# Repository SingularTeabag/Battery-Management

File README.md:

# **Battery-Management**
A repository to organize my battery management PCBs

## Single Cell 5 Volt Regulator

### Chips used
* [BQ25185DLHR](https://www.ti.com/product/BQ25185) - Battery Charging 
* [TPS61023DRLT](https://www.ti.com/product/TPS61023) - Voltage Regulation
* [MAX17048G](https://www.analog.com/en/products/max17048.html) - Fuel Gauge
### About 
This PCB is my first "real" PCB that I've designed from scratch using the datasheets of the three respective chips.
That aside this PCB is intended for easy battery support for prototyping with microcontroller development boards that require a stable 5 volt input. The board breaks out STAT1, STAT2, CE, and TS from BQ25185DLHR to allow data and control to the used microcontroller, and an external thermistor for battery safety. The board additionally has two pins meant to be used for an external on/off switch, marked on the back silkscreen. Like the battery charging IC the fuel gauges' data signals are also broken out to intended for use with the microcontroller. The USB type C port does not have it's data plus and data minus pins broken out, these are used as a differential pair which requires both wires to be exactly the same length and require impedance matching which all goes out the window when using external wires.

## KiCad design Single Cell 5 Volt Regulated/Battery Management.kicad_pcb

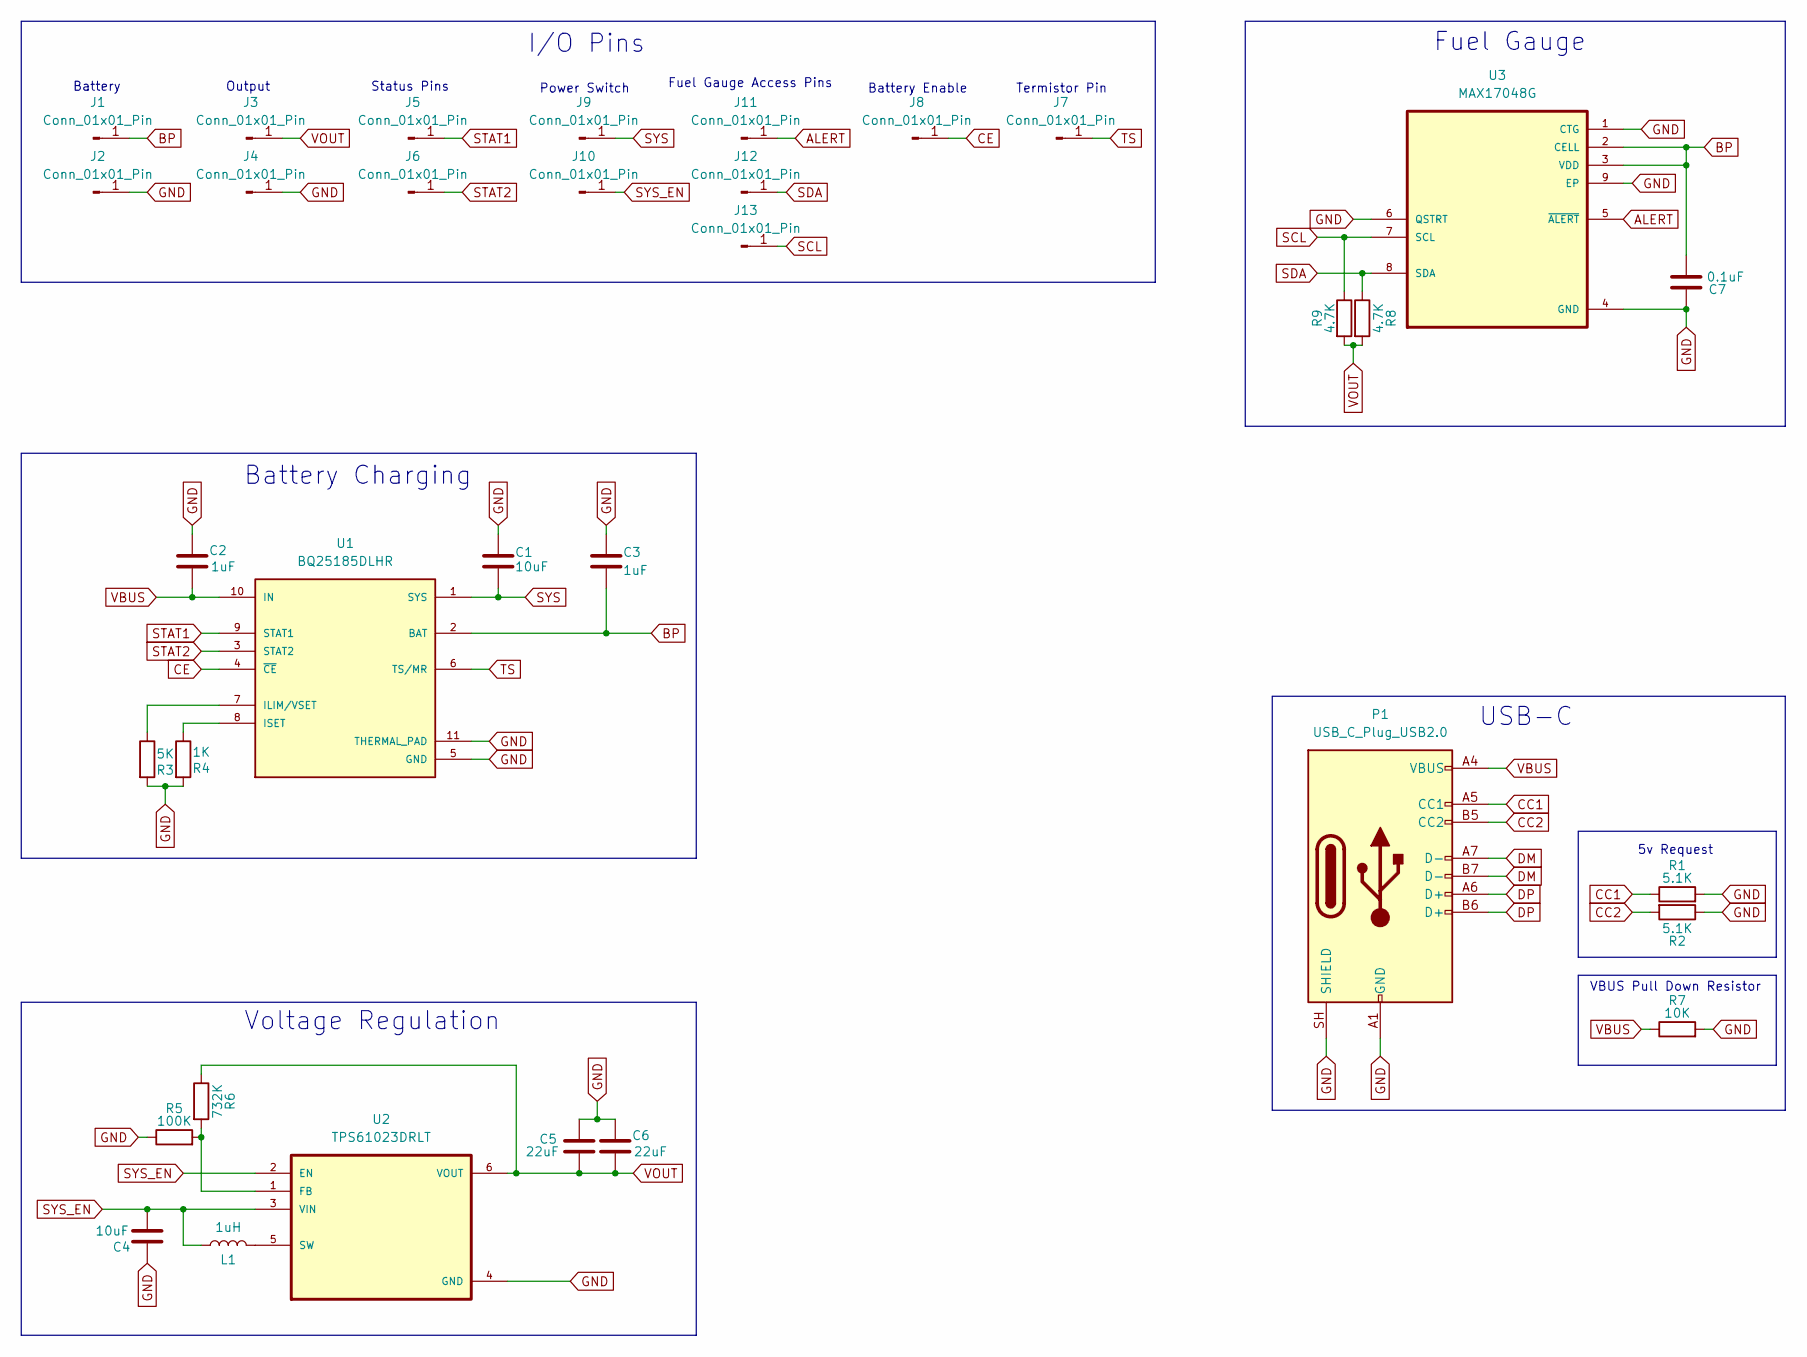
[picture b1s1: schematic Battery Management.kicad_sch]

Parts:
C1, C4: 10uF; C_0603_1608Metric
C2, C3: 1uF; C_0603_1608Metric
C5, C6: 22uF; C_0603_1608Metric
C7: 0.1uF; C_0603_1608Metric
J1, J3, J5, J6, J7, J8, J9, J10, J11, J12, J13: Conn_01x01_Pin; Connector Hole
J2, J4: Conn_01x01_Pin; Ground Hole
L1: 1uH; L_APV_ANR4030
P1: USB_C_Plug_USB2.0; USB_C_Receptacle_JAE_DX07S016JA1R1500
R1, R2: 5.1K; R_0603_1608Metric
R3: 5K; R_0603_1608Metric
R4: 1K; R_0603_1608Metric
R5: 100K; R_0603_1608Metric
R6: 732K; R_0603_1608Metric
R7: 10K; R_0603_1608Metric
R8, R9: 4.7K; R_0603_1608Metric
U1: BQ25185DLHR; IC_BQ25185DLHR; PARTREV OCTOBER 2023
U2: TPS61023DRLT; SOT50P160X60-6N
U3: MAX17048G; SON50P200X200X80-9N

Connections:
ALERT: J11.1 (Pin_1_1), U3.5 (~ALERT)
BP: C3.2, C7.1, J1.1 (Pin_1_1), U1.2 (BAT), U3.2 (CELL), U3.3 (VDD)
CC1: P1.A5 (CC1), R1.1
CC2: P1.B5 (CC2), R2.2
CE: J8.1 (Pin_1_1), U1.4 (~CE)
DM: P1.A7 (D-), P1.B7 (D-)
DP: P1.A6 (D+), P1.B6 (D+)
GND: C1.1, C2.1, C3.1, C4.1, C5.2, C6.1, C7.2, J2.1 (Pin_1_1), J4.1 (Pin_1_1), P1.A1 (GND), P1.A12 (GND), P1.B1 (GND), P1.B12 (GND), P1.SH (SHIELD), R1.2, R2.1, R3.2, R4.2, R5.1, R7.2, U1.5 (GND), U1.11 (THERMAL_PAD), U2.4 (GND), U3.1 (CTG), U3.4 (GND), U3.6 (QSTRT), U3.9 (EP)
unnamed: R3.1, U1.7 (ILIM/VSET)
unnamed: R4.1, U1.8 (ISET)
unnamed: R5.2, R6.2, U2.1 (FB)
unnamed: L1.2, U2.5 (SW)
SCL: J13.1 (Pin_1_1), R9.1, U3.7 (SCL)
SDA: J12.1 (Pin_1_1), R8.1, U3.8 (SDA)
STAT1: J5.1 (Pin_1_1), U1.9 (STAT1)
STAT2: J6.1 (Pin_1_1), U1.3 (STAT2)
SYS: C1.2, J9.1 (Pin_1_1), U1.1 (SYS)
SYS_EN: C4.2, J10.1 (Pin_1_1), L1.1, U2.2 (EN), U2.3 (VIN)
TS: J7.1 (Pin_1_1), U1.6 (TS/MR)
VBUS: C2.2, P1.A4 (VBUS), P1.A9 (VBUS), P1.B4 (VBUS), P1.B9 (VBUS), R7.1, U1.10 (IN)
VOUT: C5.1, C6.2, J3.1 (Pin_1_1), R6.1, R8.2, R9.2, U2.6 (VOUT)

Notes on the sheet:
Fuel Gauge
Battery Enable
Battery
Status Pins
Output
Voltage Regulation
Battery Charging
USB-C
5v Request
I/O Pins
Fuel Gauge Access Pins
Termistor Pin
VBUS Pull Down Resistor
Power Switch

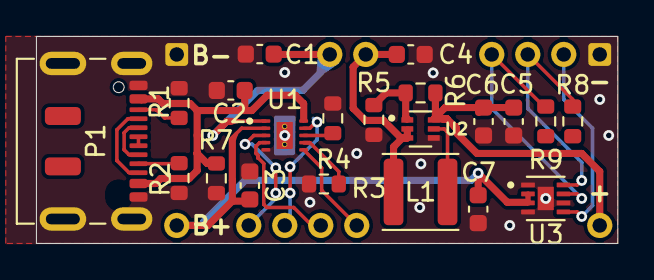
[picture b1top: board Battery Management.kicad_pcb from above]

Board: 2 copper layers, 32.3 x 11.5 mm, 34 parts (0 on the bottom side), 21 nets.
